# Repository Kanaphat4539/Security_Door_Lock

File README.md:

# Security Door Lock System (ระบบประตูเพื่อความปลอดภัยอัจฉริยะ)

โปรเจกต์ระบบควบคุมและบันทึกการเปิด-ปิดประตูห้องปฏิบัติการ/อาคารอัจฉริยะ ด้วยเทคโนโลยี RFID, กล้องตรวจจับและบันทึกใบหน้า (ESP32-CAM), เซนเซอร์วัดระยะ (Ultrasonic), ระบบแจ้งเตือนผ่าน LINE Official Account (Flex Message) และระบบรายงานผลแดชบอร์ดแบบ Real-time ผ่านเว็บ (Next.js + NestJS + WebSocket)

---

## 🏗️ โครงสร้างโปรเจกต์ (Project Structure)

- **`apps/frontend`**: เว็บแอปพลิเคชัน Dashboard (Next.js App Router + Tailwind CSS + Lucide Icons)
- **`apps/backend`**: เซิร์ฟเวอร์ API, ฐานข้อมูล Prisma ORM และ WebSocket Gateway (NestJS + MySQL)
- **`firmware/esp32-main`**: เฟิร์มแวร์ ESP32 หลักสำหรับต่อเซนเซอร์ RFID RC522, Ultrasonic HC-SR04, จอแสดงผล และรีเลย์ควบคุมกลอนแม่เหล็กไฟฟ้า
- **`firmware/esp32-cam`**: เฟิร์มแวร์ ESP32-CAM ถ่ายภาพใบหน้าเมื่อมีการทาบบัตรและส่งขึ้นเซิร์ฟเวอร์
- **`firmware/shared`**: `protocol.h` — ข้อตกลงรับ-ส่งข้อมูลผ่าน UART ระหว่าง ESP32 ทั้ง 2 บอร์ด
- **`docker`**: สคริปต์และคอนฟิกสำหรับ MySQL บน Docker Container

> [!NOTE]
> `apps/backend` และ `apps/frontend` แยก `node_modules` และ `package.json` ของตัวเอง (ไม่ใช่ monorepo workspace) ดังนั้นเวลาติดตั้งหรือรันคำสั่งต้อง `cd` เข้าไปในโฟลเดอร์ของแต่ละฝั่ง

---

## 🚀 คู่มือติดตั้งและเริ่มใช้งาน (สำหรับเพื่อน/ผู้พัฒนาใหม่)

เพื่อให้เพื่อนสามารถเปิดใช้งานเว็บไซต์และระบบทั้งหมดได้เหมือนเจ้าของโปรเจกต์ทุกประการ ให้ทำตามขั้นตอนตามลำดับดังนี้:

### 1. สิ่งที่ต้องมีในเครื่อง (Prerequisites)
- [Node.js](https://nodejs.org/) (เวอร์ชัน 18 ขึ้นไป แนะนำ LTS)
- [Docker Desktop](https://www.docker.com/products/docker-desktop/) (และเปิดใช้งานอยู่)
- [Git](https://git-scm.com/)
- [PlatformIO IDE](https://platformio.org/) (สำหรับเขียนและแฟลชโค้ดลงบอร์ด ESP32)

---

### 2. ติดตั้งและเปิดฐานข้อมูล (Database)
เปิด Terminal ที่โฟลเดอร์หลักของโปรเจกต์ (`Security Door Lock/`):

```bash
docker compose up -d --wait
```
*ระบบจะเปิด MySQL 8.4 ขึ้นมาบนพอร์ต **3307** (เพื่อป้องกันการชนกับพอร์ต 3306 เดิมในเครื่อง)*

---

### 3. ตั้งค่าและเปิดใช้งานเซิร์ฟเวอร์ Backend (NestJS)

เปิด Terminal แล้วเข้าไปที่โฟลเดอร์ `apps/backend`:

```bash
cd apps/backend
npm install
npm run setup          # สร้างไฟล์ .env พร้อมสุ่ม Token/Secret ความปลอดภัยให้อัตโนมัติ
npm run db:generate    # สร้าง Prisma Client
npm run db:migrate     # รันตารางฐานข้อมูลลง MySQL
```

#### 3.1 สร้างบัญชีผู้ใช้งานสำหรับเข้าเว็บไซต์ (จำเป็น!)
ก่อนจะล็อกอินเข้าเว็บ ต้องมีบัญชีผู้ใช้งานในระบบก่อน โดยสามารถเลือกวิธีใดวิธีหนึ่ง:

- **สร้างบัญชีผู้ดูแลระบบ (ADMIN):**
  ```bash
  npm run db:add-admin -- admin "รหัสผ่าน8ตัวขึ้นไป" ADMIN
  ```
  *(สามารถเปลี่ยน `admin` เป็นชื่อผู้ใช้ที่ต้องการ และรหัสผ่านต้องยาว 8 ตัวขึ้นไป)*

- **หรือ สร้างบัญชีเจ้าหน้าที่รักษาความปลอดภัย (GUARD):**
  ```bash
  npm run db:add-admin -- guard "รหัสผ่าน8ตัวขึ้นไป" GUARD
  ```

- **หรือ สมัครผ่านหน้าเว็บ (`/register`):**
  สามารถเปิดดูค่า `ADMIN_INVITE_CODE` ในไฟล์ `apps/backend/.env` แล้วนำโค้ดนั้นไปกรอกที่หน้าลงทะเบียนบนเว็บ

#### 3.2 เพิ่มบัตร RFID เข้าระบบ
หากมีบัตร RFID สามารถเพิ่มหรือผูกชื่อผู้ถือบัตรล่วงหน้าได้ด้วยคำสั่ง:
```bash
npm run db:add-card -- A9620207 "ชื่อผู้ถือบัตร"
```
*(หากทาบบัตรที่ไม่เคยลงทะเบียน ระบบจะปฏิเสธ (DENIED) และแสดง UID ใน Terminal Backend สามารถนำ UID นั้นมาเพิ่มต่อได้ทันที)*

#### 3.3 ตั้งค่าการแจ้งเตือน LINE Bot (ถ้าต้องการ)
หากต้องการให้แจ้งเตือนการสแกนบัตร (Flex Message) เข้ากลุ่ม LINE:
1. เปิดไฟล์ `apps/backend/.env`
2. ใส่ Token และ Group ID:
   ```env
   LINE_CHANNEL_ACCESS_TOKEN=ใส่_Channel_Access_Token_ที่นี่
   LINE_GROUP_ID=ใส่_Group_ID_ที่นี่
   ```
3. ดึง Bot เข้ากลุ่ม LINE และเปิดตั้งค่า "Allow account to join groups" ใน LINE Official Account Manager
4. ทดสอบส่งข้อความเข้ากลุ่ม:
   ```bash
   npm run test:line
   ```

#### 3.4 รัน Backend
```bash
npm run start:dev
```
*Backend จะพร้อมให้บริการที่: **http://localhost:3001***

---

### 4. ตั้งค่าและเปิดใช้งาน Frontend Dashboard (Next.js)

เปิด Terminal อีกหน้าต่าง แล้วเข้าไปที่โฟลเดอร์ `apps/frontend`:

```bash
cd apps/frontend
npm install
cp .env.example .env.local
npm run dev
```

*เปิดเว็บเบราว์เซอร์แล้วไปที่: **http://localhost:3000***  
เข้าสู่ระบบด้วยชื่อผู้ใช้และรหัสผ่านที่สร้างไว้ในขั้นตอน **3.1**

---

## 🌐 วิธีให้เพื่อนเข้าใช้งานเว็บจากเครื่องอื่น (แชร์ผ่าน Wi-Fi / LAN วงเดียวกัน)

หากต้องการให้เพื่อนบนเครือข่าย Wi-Fi เดียวกัน เข้าใช้งาน Dashboard ผ่านมือถือหรือคอมพิวเตอร์ของเพื่อน:

1. **หาหมายเลข IP เครื่องของท่าน (Host IP):**
   - บน Windows: เปิด PowerShell พิมพ์ `ipconfig` แล้วดู IPv4 Address (เช่น `192.168.1.50`)
2. **แก้ไขไฟล์ `apps/frontend/.env.local`:**
   ให้ชี้ไปยัง IP เครื่องโฮสต์แทน localhost:
   ```env
   NEXT_PUBLIC_API_URL=http://192.168.1.50:3001
   NEXT_PUBLIC_SOCKET_URL=http://192.168.1.50:3001
   ```
3. **รัน Frontend ให้รับการเชื่อมต่อจากภายนอก:**
   ```bash
   npm run dev -- -H 0.0.0.0
   ```
4. **ให้เพื่อนเปิดเบราว์เซอร์ไปที่:**
   ```
   http://192.168.1.50:3000
   ```
   และล็อกอินด้วยบัญชี ADMIN หรือ GUARD ที่สร้างไว้

---

## 💻 ฟังก์ชันและการใช้งานระบบเว็บ (Web Features)

### 1. ระบบยืนยันตัวตนและการเข้าถึง (Authentication & Roles)
- **ADMIN**: สิทธิ์สูงสุด สามารถจัดการข้อมูลผู้ใช้, เพิ่ม/ลบ/แก้ไขบัตร RFID, ตั้งค่าอีเมลแจ้งเตือนรายบุคคล, ดูประวัติเข้า-ออกพร้อมภาพถ่าย, สั่งปลดล็อกประตูระยะไกล (Remote Unlock) และจัดการบัญชีผู้ตรวจการ (Guard)
- **GUARD**: สิทธิ์เจ้าหน้าที่รักษาความปลอดภัย มอนิเตอร์หน้าจอ Dashboard และดูประวัติการเข้า-ออกย้อนหลังแบบเรียลไทม์

### 2. หน้าระบบต่างๆ
- **`/admin/dashboard`**: แสดงภาพรวมระบบแบบ Real-time, สถิติการเข้า-ออกรายวัน, สถานะการเชื่อมต่อ และปุ่ม Emergency Unlock สั่งเปิดประตูฉุกเฉิน
- **`/admin/users`**: หน้าจัดการข้อมูลผู้ถือบัตร RFID (UID, ชื่อ-สกุล, สถานะบัตร Active/Inactive, อีเมลสำหรับรับการแจ้งเตือน)
- **`/admin/logs`**: รายการประวัติการเข้า-ออกทั้งหมด พร้อมระบุทิศทาง (เข้า/ออก), สถานะ (GRANTED / DENIED) และภาพถ่าย Snapshot จาก ESP32-CAM แบบทันที
- **`/admin/guards`**: จัดการสร้างและลบบัญชีผู้ตรวจการ (Guard)
- **`/guard/dashboard`**: จอมอนิเตอร์สำหรับเจ้าหน้าที่รักษาความปลอดภัย

---

## 🔌 การตั้งค่าฝั่งฮาร์ดแวร์ (Firmware ESP32)

แต่ละบอร์ดเป็นโปรเจกต์ PlatformIO แยกกัน:

### 1. ESP32-CAM (กล้องถ่ายภาพใบหน้า)
```bash
cd firmware/esp32-cam
cp src/secrets.example.h src/secrets.h
```
แก้ไขไฟล์ `src/secrets.h`:
- ใส่ชื่อ Wi-Fi (`WIFI_SSID`) และรหัสผ่าน (`WIFI_PASS`)
- ใส่ `DEVICE_TOKEN` ให้ตรงกับค่าใน `apps/backend/.env`
- แฟลชโค้ดลงบอร์ด: `pio run -t upload`

### 2. ESP32-Main (ควบคุมกลอนประตู, RFID, Ultrasonic)
```bash
cd firmware/esp32-main
cp src/secrets.example.h src/secrets.h   # ถ้ามี
pio run -t upload
```

---

## 📧 ระบบแจ้งเตือนผ่าน Email (Resend)

1. รันการอัปเดต Migration ฐานข้อมูล:
   ```bash
   cd apps/backend
   npm run db:deploy
   npm run db:generate
   ```
2. สมัครใช้งานและยืนยันโดเมนที่ [Resend](https://resend.com/docs/dashboard/domains/introduction)
3. เพิ่มค่าลงใน `apps/backend/.env`:
   ```env
   RESEND_API_KEY=re_xxxxxxxxxxxx
   EMAIL_FROM="Door Lock <alerts@your-domain.com>"
   ```
4. ในหน้า **Admin &rarr; User Management** ให้ใส่อีเมลของผู้ถือบัตร แล้วติ๊กเปิดใช้งาน **Email owner on each granted scan**

---

## 🛠️ สรุปคำสั่งที่ใช้งานบ่อย (Cheat Sheet)

| คำสั่ง | ตำแหน่งที่รัน | หน้าที่ |
|---|---|---|
| `docker compose up -d --wait` | Root (`/`) | เปิดใช้งานฐานข้อมูล MySQL |
| `docker compose down` | Root (`/`) | หยุดการทำงานของฐานข้อมูล |
| `npm run start:dev` | `apps/backend` | เริ่มทำงานเซิร์ฟเวอร์ Backend (พอร์ต 3001) |
| `npm run db:add-admin -- <user> <pass> [ROLE]` | `apps/backend` | สร้างหรือเปลี่ยนรหัสผ่านบัญชี ADMIN/GUARD |
| `npm run db:add-card -- <UID> "<Name>"` | `apps/backend` | เพิ่มหรือเปิดใช้งานบัตร RFID เข้าระบบ |
| `npm run test:line` | `apps/backend` | ทดสอบยิงข้อความแจ้งเตือนเข้า LINE Bot |
| `npm run db:studio` | `apps/backend` | เปิดดูข้อมูลในฐานข้อมูลผ่านหน้าเว็บ Prisma Studio |
| `npm run dev` | `apps/frontend` | เริ่มทำงานเว็บ Frontend Dashboard (พอร์ต 3000) |

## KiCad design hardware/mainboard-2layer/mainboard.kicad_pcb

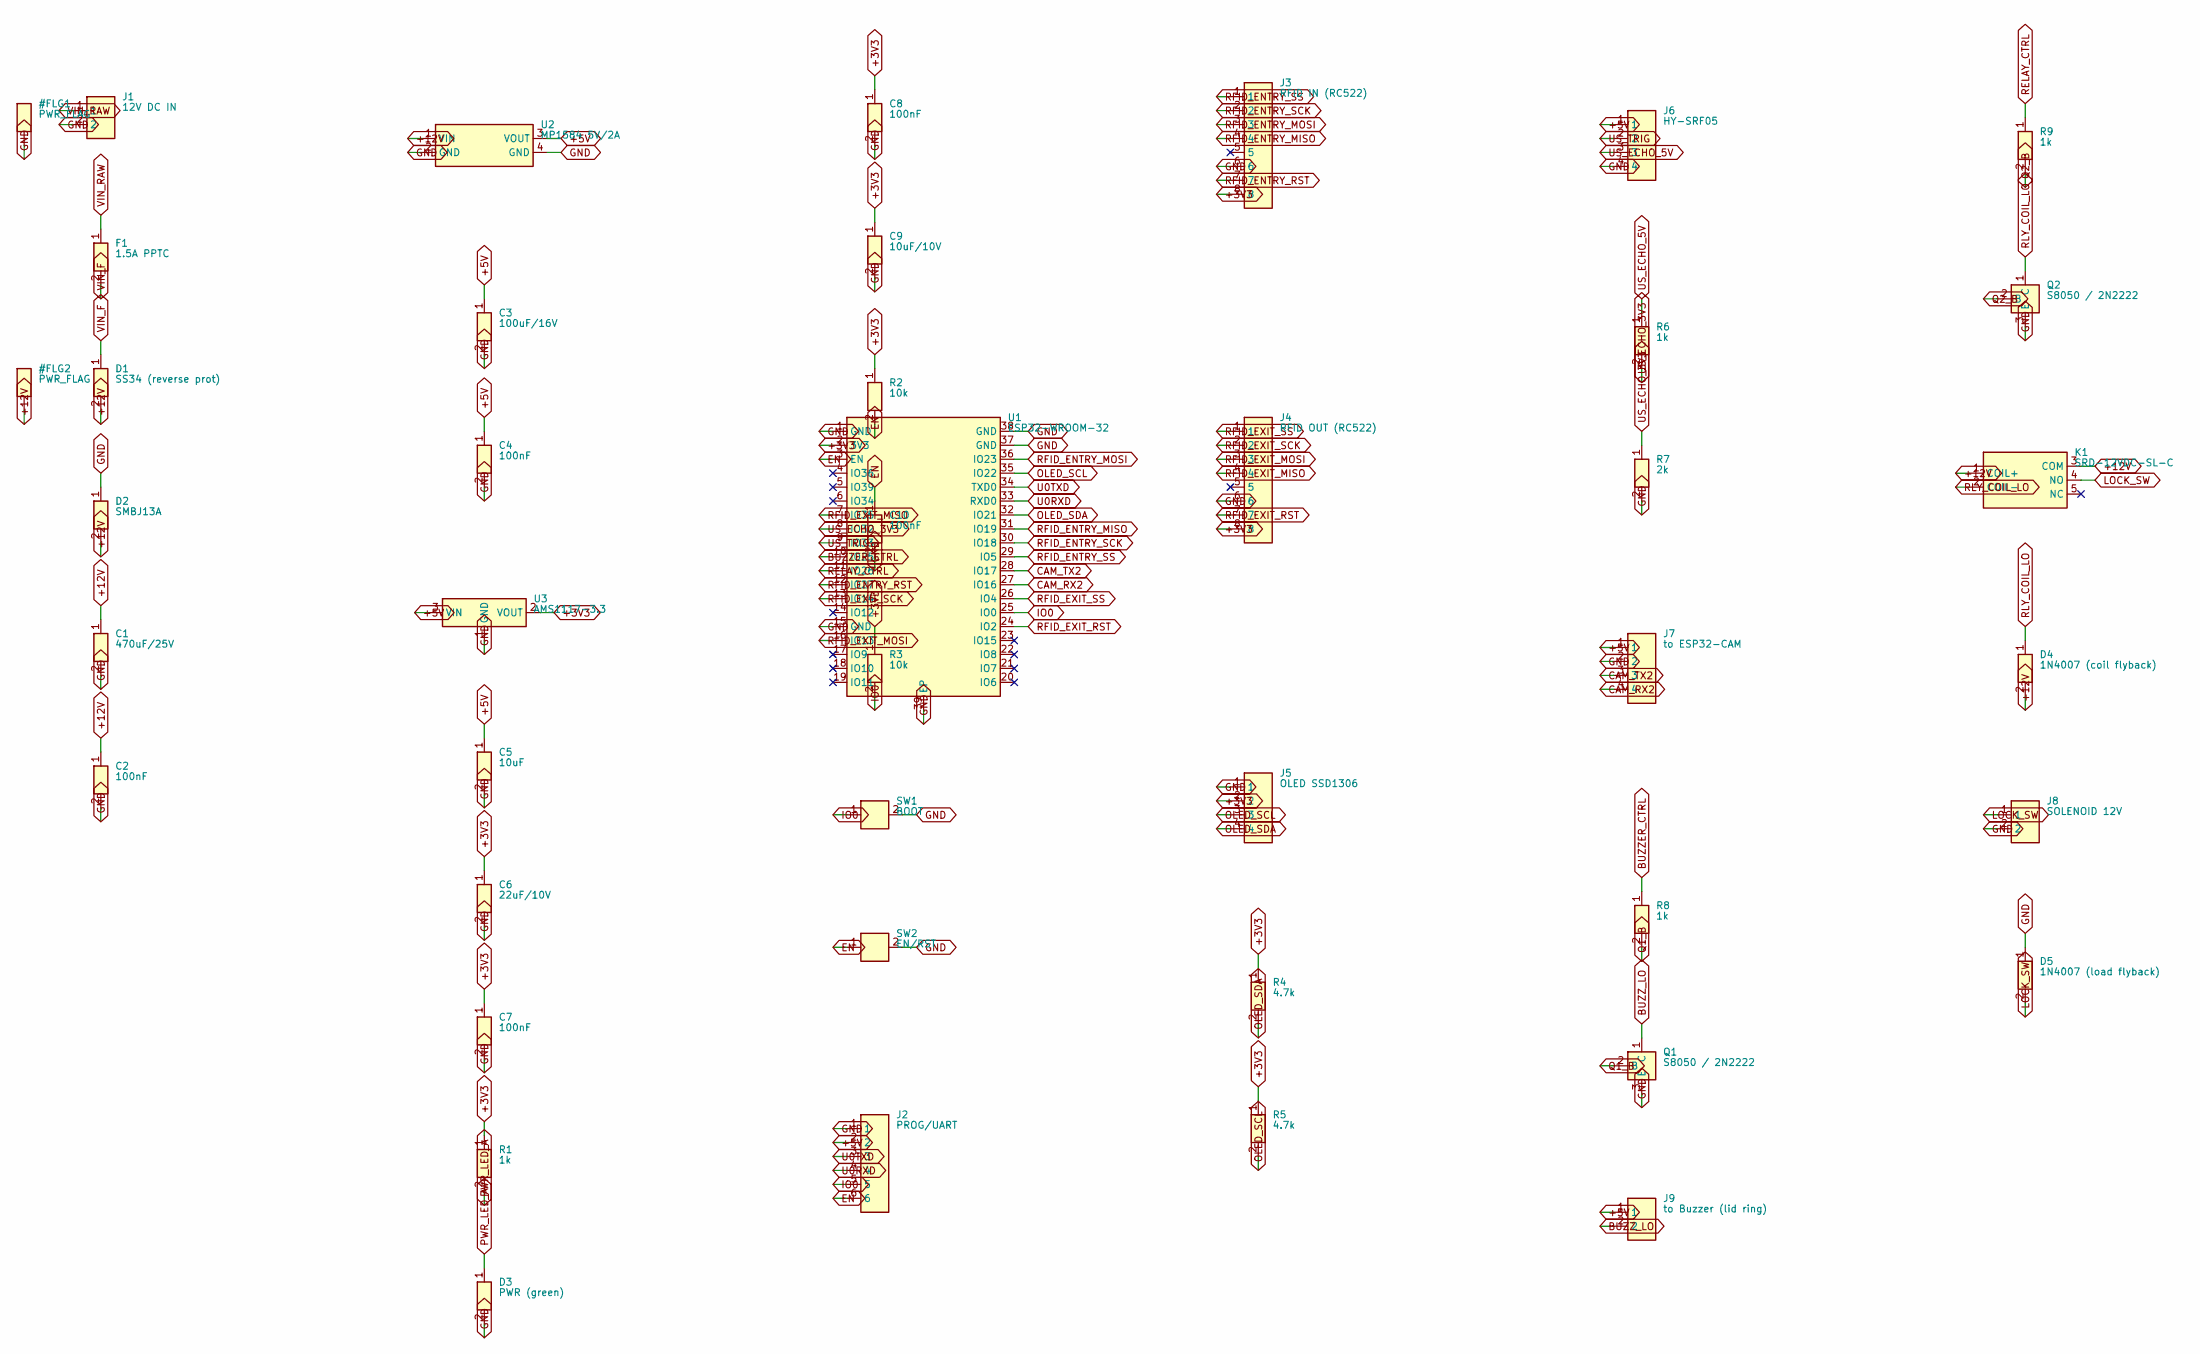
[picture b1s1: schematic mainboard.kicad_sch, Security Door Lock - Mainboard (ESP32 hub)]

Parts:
C1: 470uF/25V; CP_Radial_D8.0mm_P3.50mm
C2, C4, C7, C8, C10: 100nF; C_0805_2012Metric
C3: 100uF/16V; CP_Radial_D8.0mm_P3.50mm
C5: 10uF; C_0805_2012Metric
C6: 22uF/10V; CP_Radial_D8.0mm_P3.50mm
C9: 10uF/10V; CP_Radial_D8.0mm_P3.50mm
D1: SS34 (reverse prot); D_SMA
D2: SMBJ13A; D_SMA
D3: PWR (green); LED_0805_2012Metric
D4: 1N4007 (coil flyback); D_SMA
D5: 1N4007 (load flyback); D_SMA
F1: 1.5A PPTC; Fuse_1812_4532Metric
J1: 12V DC IN; TerminalBlock_Phoenix_MKDS-1,5-2-5.08_1x02_P5.08mm_Horizont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
J2: PROG/UART; PinHeader_1x06_P2.54mm_Vertical
J3: RFID IN (RC522); PinHeader_1x08_P2.54mm_Vertical
J4: RFID OUT (RC522); PinHeader_1x08_P2.54mm_Vertical
J5: OLED SSD1306; PinHeader_1x04_P2.54mm_Vertical
J6: HY-SRF05; PinHeader_1x04_P2.54mm_Vertical
J7: to ESP32-CAM; PinHeader_1x04_P2.54mm_Vertical
J8: SOLENOID 12V; TerminalBlock_Phoenix_MKDS-1,5-2-5.08_1x02_P5.08mm_Horizont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
J9: to Buzzer (lid ring); PinHeader_1x02_P2.54mm_Vertical
K1: SRD-12VDC-SL-C; Relay_SPDT_SANYOU_SRD_Series_Form_C
Q1, Q2: S8050 / 2N2222; SOT-23
R1, R6, R8, R9: 1k; R_0805_2012Metric
R2, R3: 10k; R_0805_2012Metric
R4, R5: 4.7k; R_0805_2012Metric
R7: 2k; R_0805_2012Metric
SW1: BOOT; SW_PUSH_6mm
SW2: EN/RST; SW_PUSH_6mm
U1: ESP32-WROOM-32
U2: MP1584 5V/2A; PinHeader_1x04_P2.54mm_Vertical
U3: AMS1117-3.3; SOT-223-3_TabPin2

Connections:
+3V3: C6.1 (+), C7.1, C8.1, C9.1 (+), J3.8, J4.8, J5.2, R1.1, R2.1, R3.1, R4.1, R5.1, U1.2 (3V3), U3.2 (VOUT)
+5V: C3.1 (+), C4.1, C5.1, J2.2, J6.1, J7.1, J9.1, U2.3 (VOUT), U3.3 (VIN)
+12V: C1.1 (+), C2.1, D1.2 (K), D2.2 (K), D4.2 (K), K1.1 (COIL+), K1.3 (COM), U2.1 (VIN)
BUZZER_CTRL: R8.1, U1.10 (IO25)
BUZZ_LO: J9.2, Q1.1 (C)
CAM_RX2: J7.4, U1.27 (IO16)
CAM_TX2: J7.3, U1.28 (IO17)
EN: C10.1, J2.6, R2.2, SW2.1, U1.3 (EN)
GND: C1.2 (-), C2.2, C3.2 (-), C4.2, C5.2, C6.2 (-), C7.2, C8.2, C9.2 (-), C10.2, D2.1 (A), D3.2 (K), D5.1 (A), J1.2, J2.1, J3.6, J4.6, J5.1, J6.4, J7.2, J8.2, Q1.3 (E), Q2.3 (E), R7.2, SW1.2, SW2.2, U1.1 (GND), U1.15 (GND), U1.37 (GND), U1.38 (GND), U1.39 (EP), U2.2 (GND), U2.4 (GND), U3.1 (GND)
IO0: J2.5, R3.2, SW1.1, U1.25 (IO0)
LOCK_SW: D5.2 (K), J8.1, K1.4 (NO)
OLED_SCL: J5.3, R5.2, U1.35 (IO22)
OLED_SDA: J5.4, R4.2, U1.32 (IO21)
PWR_LED_A: D3.1 (A), R1.2
Q1_B: Q1.2 (B), R8.2
Q2_B: Q2.2 (B), R9.2
RELAY_CTRL: R9.1, U1.11 (IO26)
RFID_ENTRY_MISO: J3.4, U1.31 (IO19)
RFID_ENTRY_MOSI: J3.3, U1.36 (IO23)
RFID_ENTRY_RST: J3.7, U1.12 (IO27)
RFID_ENTRY_SCK: J3.2, U1.30 (IO18)
RFID_ENTRY_SS: J3.1, U1.29 (IO5)
RFID_EXIT_MISO: J4.4, U1.7 (IO35)
RFID_EXIT_MOSI: J4.3, U1.16 (IO13)
RFID_EXIT_RST: J4.7, U1.24 (IO2)
RFID_EXIT_SCK: J4.2, U1.13 (IO14)
RFID_EXIT_SS: J4.1, U1.26 (IO4)
RLY_COIL_LO: D4.1 (A), K1.2 (COIL-), Q2.1 (C)
U0RXD: J2.4, U1.33 (RXD0)
U0TXD: J2.3, U1.34 (TXD0)
US_ECHO_3V3: R6.2, R7.1, U1.8 (IO32)
US_ECHO_5V: J6.3, R6.1
US_TRIG: J6.2, U1.9 (IO33)
VIN_F: D1.1 (A), F1.2
VIN_RAW: F1.1, J1.1

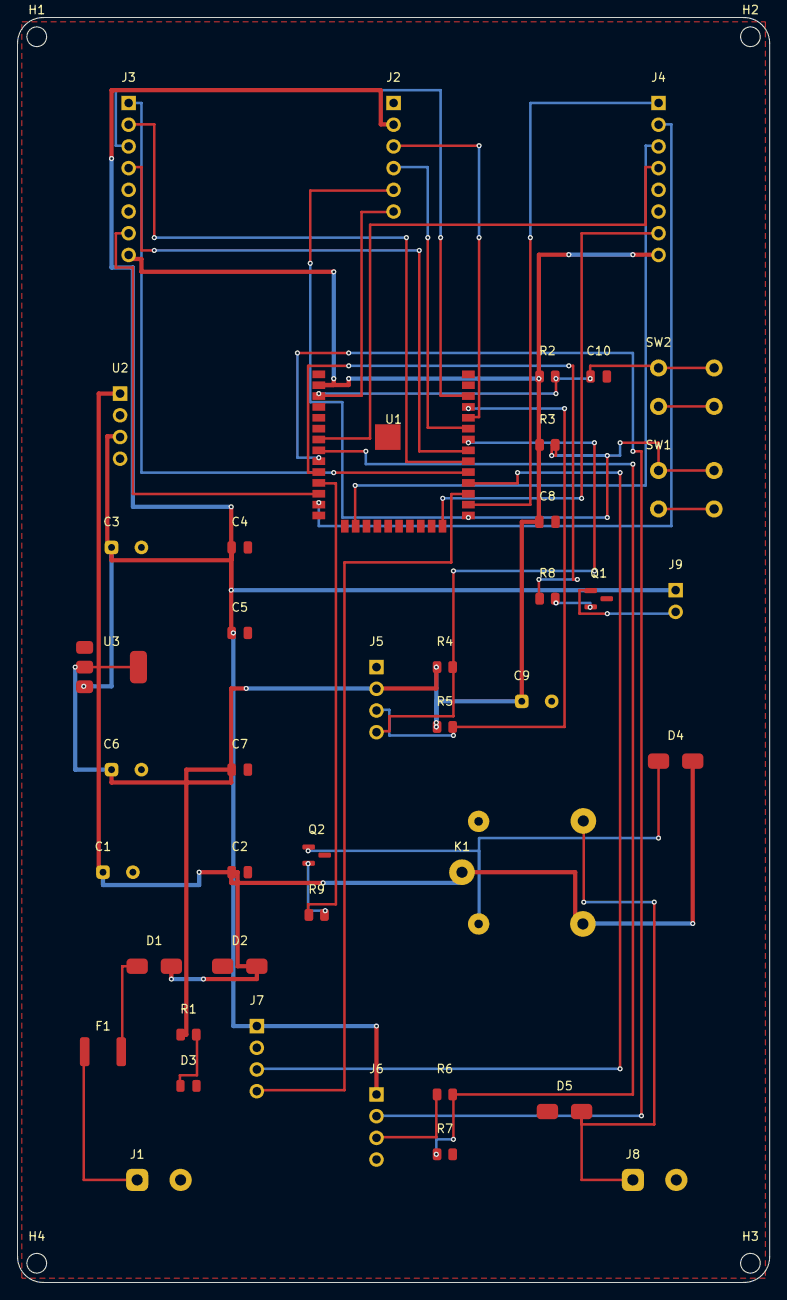
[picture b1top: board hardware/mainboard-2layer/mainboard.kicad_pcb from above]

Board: 2 copper layers, 88.0 x 148.0 mm, 46 parts (0 on the bottom side), 35 nets.

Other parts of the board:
H1, H2, H3, H4: MountingHole_2.3mm_M2_custom

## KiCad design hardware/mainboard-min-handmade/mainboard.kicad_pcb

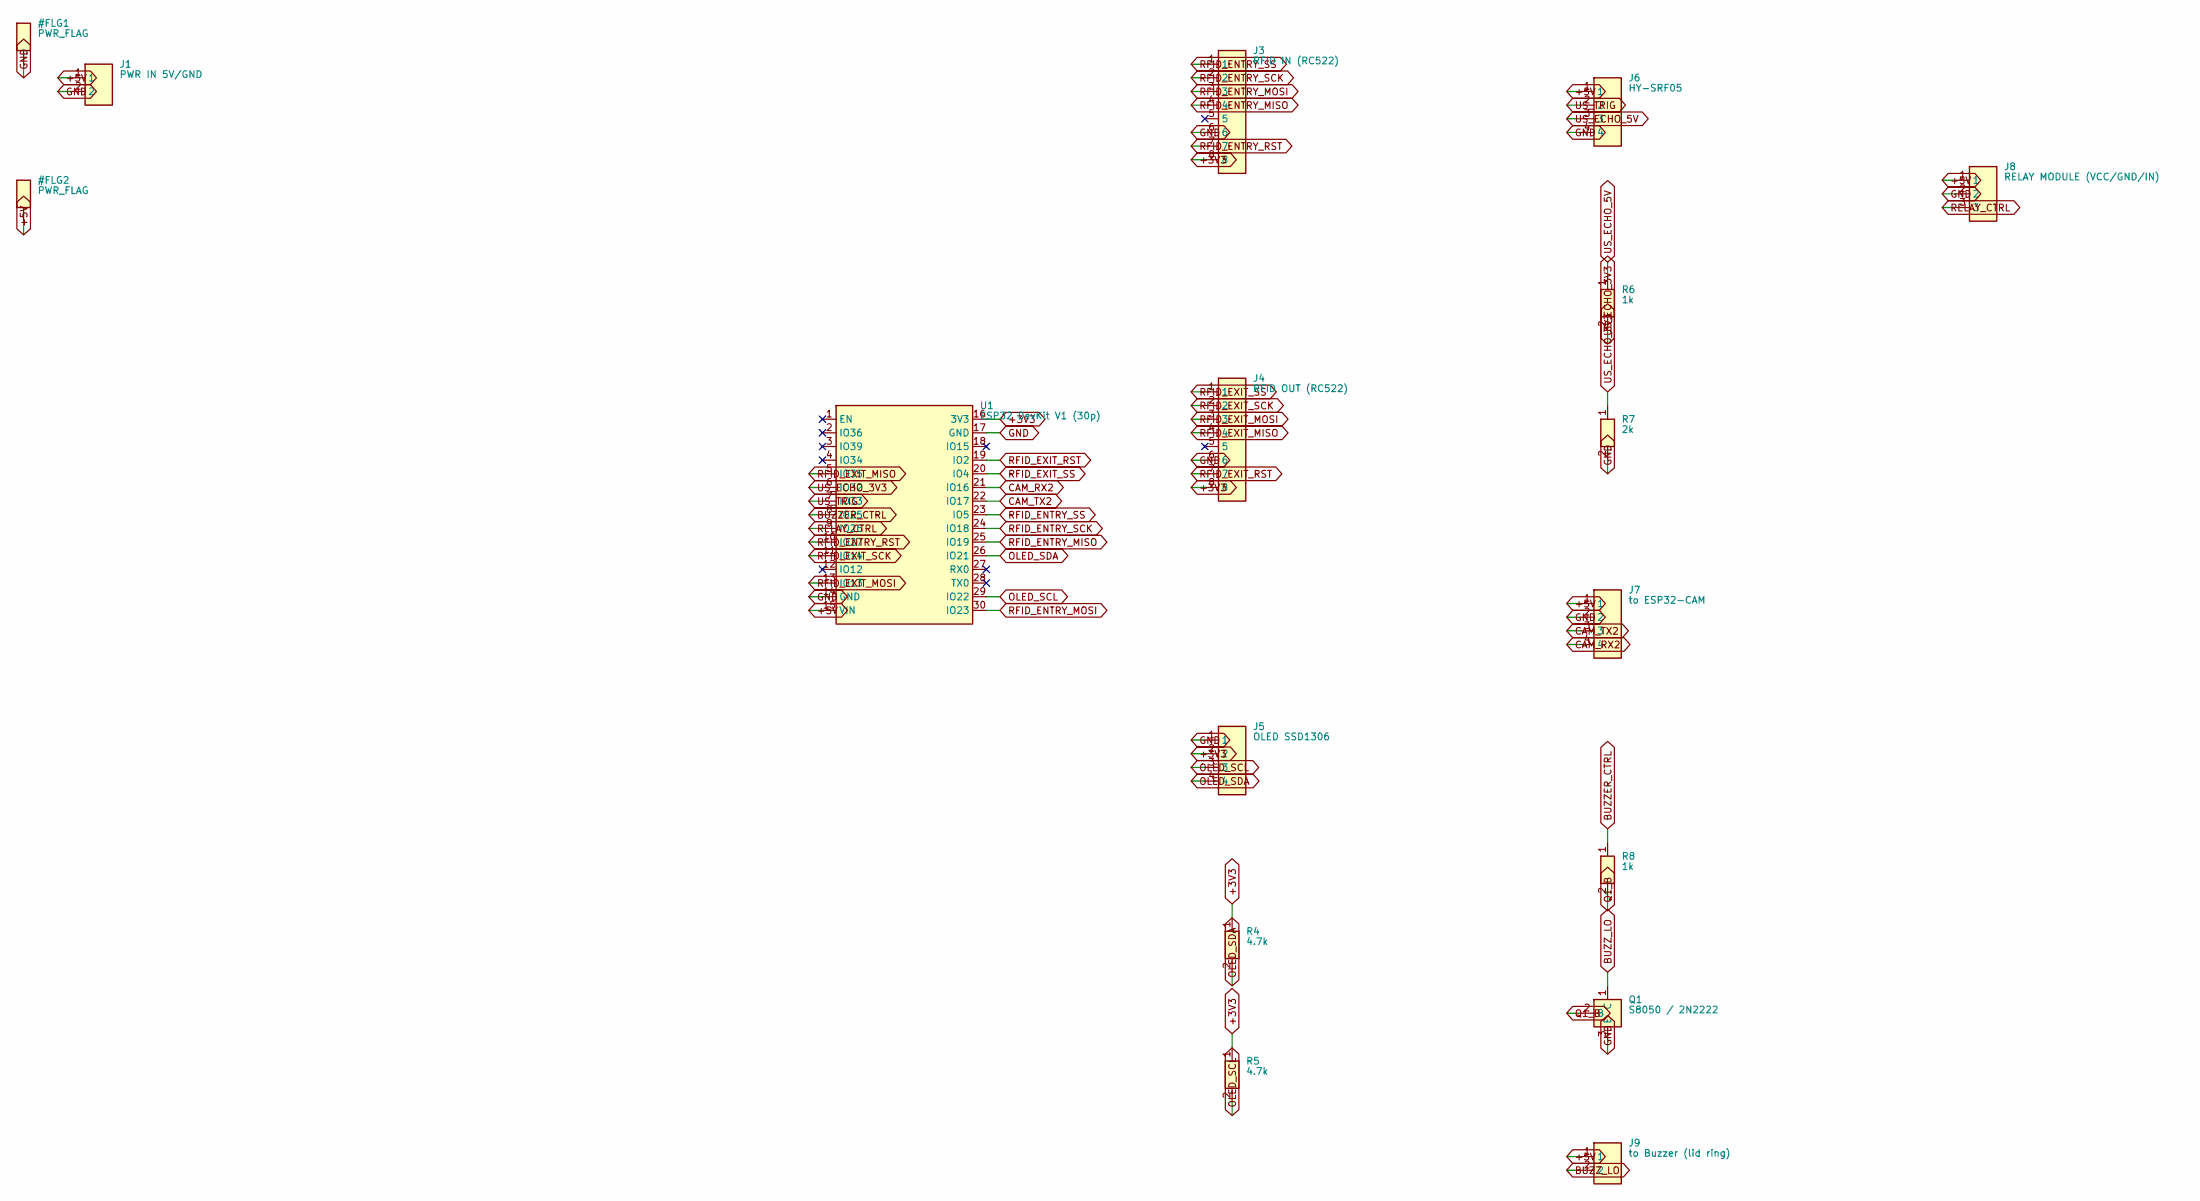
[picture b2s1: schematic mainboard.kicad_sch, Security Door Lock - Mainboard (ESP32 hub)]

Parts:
J1: PWR IN 5V/GND; PinHeader_1x02_P2.54mm_Vertical
J3: RFID IN (RC522); PinHeader_1x08_P2.54mm_Vertical
J4: RFID OUT (RC522); PinHeader_1x08_P2.54mm_Vertical
J5: OLED SSD1306; PinHeader_1x04_P2.54mm_Vertical
J6: HY-SRF05; PinHeader_1x04_P2.54mm_Vertical
J7: to ESP32-CAM; PinHeader_1x04_P2.54mm_Vertical
J8: RELAY MODULE (VCC/GND/IN); PinHeader_1x03_P2.54mm_Vertical
J9: to Buzzer (lid ring); PinHeader_1x02_P2.54mm_Vertical
Q1: S8050 / 2N2222; SOT-23
R4, R5: 4.7k; R_0805_2012Metric
R6, R8: 1k; R_0805_2012Metric
R7: 2k; R_0805_2012Metric
U1: ESP32 DevKit V1 (30p); ESP32-DevKitV1-30P_Socket

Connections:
+3V3: J3.8, J4.8, J5.2, R4.1, R5.1, U1.16 (3V3)
+5V: J1.1, J6.1, J7.1, J8.1, J9.1, U1.15 (VIN)
BUZZER_CTRL: R8.1, U1.8 (IO25)
BUZZ_LO: J9.2, Q1.1 (C)
CAM_RX2: J7.4, U1.21 (IO16)
CAM_TX2: J7.3, U1.22 (IO17)
GND: J1.2, J3.6, J4.6, J5.1, J6.4, J7.2, J8.2, Q1.3 (E), R7.2, U1.14 (GND), U1.17 (GND)
OLED_SCL: J5.3, R5.2, U1.29 (IO22)
OLED_SDA: J5.4, R4.2, U1.26 (IO21)
Q1_B: Q1.2 (B), R8.2
RELAY_CTRL: J8.3, U1.9 (IO26)
RFID_ENTRY_MISO: J3.4, U1.25 (IO19)
RFID_ENTRY_MOSI: J3.3, U1.30 (IO23)
RFID_ENTRY_RST: J3.7, U1.10 (IO27)
RFID_ENTRY_SCK: J3.2, U1.24 (IO18)
RFID_ENTRY_SS: J3.1, U1.23 (IO5)
RFID_EXIT_MISO: J4.4, U1.5 (IO35)
RFID_EXIT_MOSI: J4.3, U1.13 (IO13)
RFID_EXIT_RST: J4.7, U1.19 (IO2)
RFID_EXIT_SCK: J4.2, U1.11 (IO14)
RFID_EXIT_SS: J4.1, U1.20 (IO4)
US_ECHO_3V3: R6.2, R7.1, U1.6 (IO32)
US_ECHO_5V: J6.3, R6.1
US_TRIG: J6.2, U1.7 (IO33)

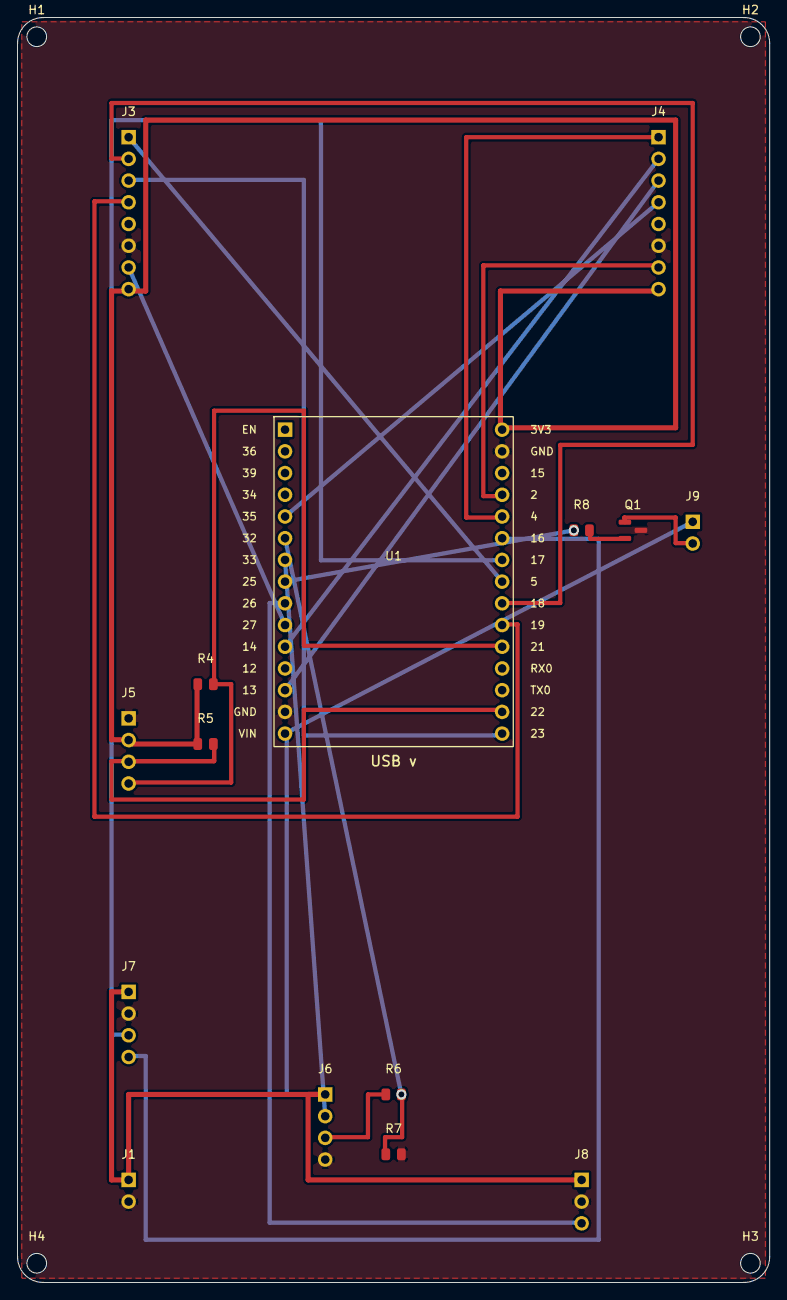
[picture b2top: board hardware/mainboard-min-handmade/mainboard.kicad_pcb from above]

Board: 2 copper layers, 88.0 x 148.0 mm, 19 parts (0 on the bottom side), 24 nets.

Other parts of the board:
H1, H2, H3, H4: MountingHole_2.3mm_M2_custom
